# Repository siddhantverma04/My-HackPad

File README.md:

# My HackPad

A custom 3×3 macropad designed from scratch using KiCad, Fusion 360, and QMK.

The HackPad uses a Seeed Studio XIAO RP2040, 9 mechanical switches,
4 SK6812MINI-E RGB LEDs, a 128×32 OLED display, and custom QMK firmware.

## Features

- 3×3 mechanical key layout
- 4 SK6812MINI-E RGB LEDs
- 0.91" 128×32 SSD1306 OLED
- Seeed Studio XIAO RP2040
- Custom PCB
- Custom 3D-printed case
- QMK firmware

## HackPad Render

## Schematic

## PCB

## Case

The case was designed to fit the custom PCB, switches, OLED, and XIAO RP2040. 

## Firmware

The HackPad runs QMK firmware on the XIAO RP2040.

Current normal keymap:

| 1 | 2 | 3 |
|---|---|---|
| 4 | 5 | 6 |
| 7 | 8 | 9 |

Holding key 9 opens an RGB-control layer for changing effects,
hue, saturation, and brightness.

## Fully assembled!

The final and fully assembled hackpad!

## Bill of Materials

| Component | Amount |
|---|---:|
| Seeed Studio XIAO RP2040 | 1 |
| Cherry MX-compatible switches | 9 |
| 1N4148 diodes | 9 |
| SK6812MINI-E RGB LEDs | 4 |
| 0.91" 128×32 SSD1306 OLED | 1 |
| 1U keycaps | 9 |
| Custom PCB | 1 |
| 3D-printed top case / plate(I will print myself) | 1 |
| 3D-printed bottom case(I will print myself) | 1 |
| M3 screws | 4 |
| M3 heat-set inserts | 4 |

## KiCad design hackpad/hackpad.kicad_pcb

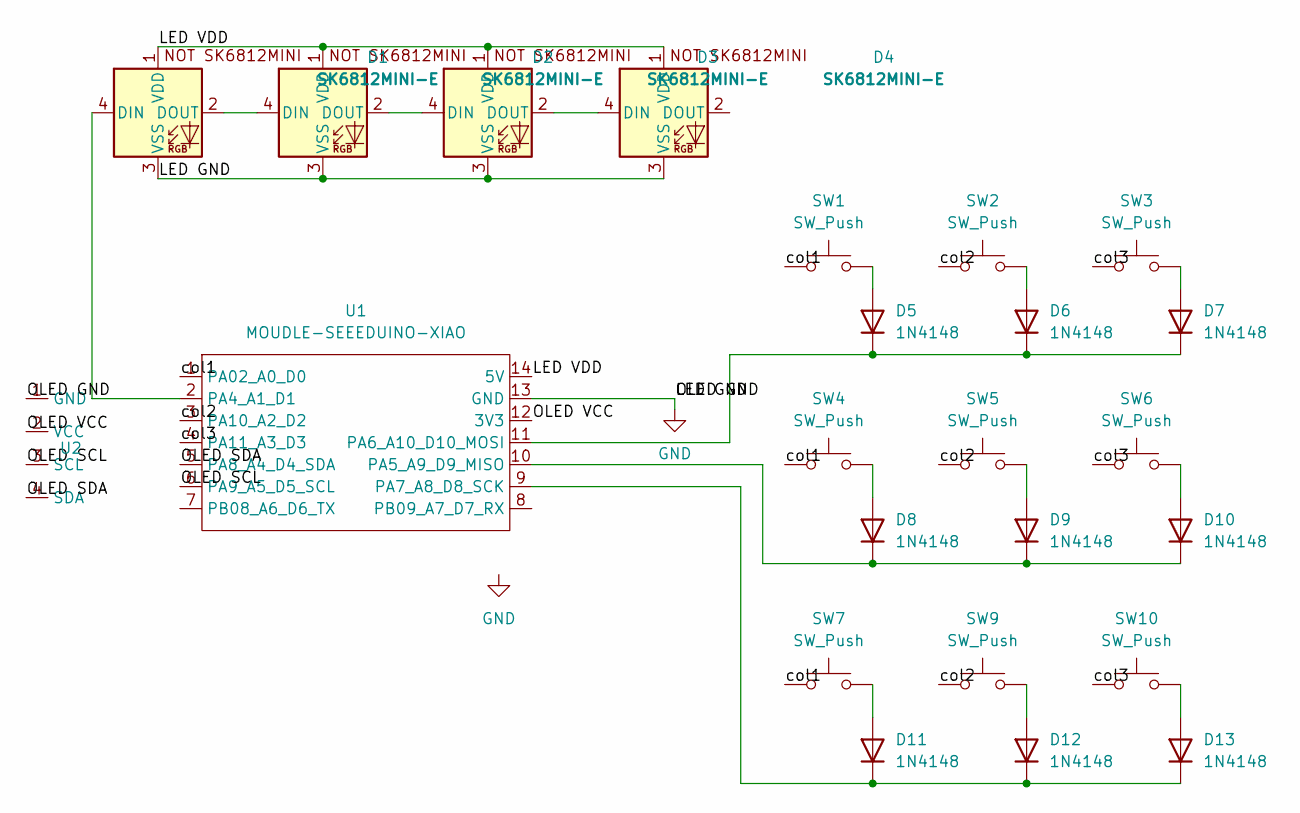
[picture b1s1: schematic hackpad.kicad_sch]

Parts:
D1, D2, D3, D4: SK6812MINI-E; LED_SK6812MINI-E_3.2x2.8mm_P1.5mm_ReverseMount
D5, D6, D7, D8, D9, D10, D11, D12, D13: 1N4148; D_DO-35_SOD27_P7.62mm_Horizontal
SW1, SW2, SW3, SW4, SW5, SW6, SW7, SW9, SW10: SW_Push; SW_Cherry_MX_1.00u_PCB
U1: MOUDLE-SEEEDUINO-XIAO; XIAO-Generic-Hybrid-14P-2.54-21X17.8MM
U2: SSD1306-0.91-OLED-4pin-128x32

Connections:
/<NO NET>: U1.5 (PA8_A4_D4_SDA), U2.4 (SDA)
/LED VDD: D1.1 (VDD), D2.1 (VDD), D3.1 (VDD), D4.1 (VDD), U1.14 (5V)
/OLED SCL: U1.6 (PA9_A5_D5_SCL), U2.3 (SCL)
/OLED VCC: U1.12 (3V3), U2.2 (VCC)
/col1: SW1.1, SW4.1, SW7.1, U1.1 (PA02_A0_D0)
/col2: SW2.1, SW5.1, SW9.1, U1.3 (PA10_A2_D2)
/col3: SW3.1, SW6.1, SW10.1, U1.4 (PA11_A3_D3)
GND: D1.3 (VSS), D2.3 (VSS), D3.3 (VSS), D4.3 (VSS), U1.13 (GND), U2.1 (GND)
unnamed: D1.4 (DIN), U1.2 (PA4_A1_D1)
unnamed: D1.2 (DOUT), D2.4 (DIN)
unnamed: D2.2 (DOUT), D3.4 (DIN)
unnamed: D3.2 (DOUT), D4.4 (DIN)
unnamed: D5.2 (A), SW1.2
unnamed: D5.1 (K), D6.1 (K), D7.1 (K), U1.11 (PA6_A10_D10_MOSI)
unnamed: D6.2 (A), SW2.2
unnamed: D7.2 (A), SW3.2
unnamed: D8.2 (A), SW4.2
unnamed: D9.2 (A), SW5.2
unnamed: D10.2 (A), SW6.2
unnamed: D8.1 (K), D9.1 (K), D10.1 (K), U1.10 (PA5_A9_D9_MISO)
unnamed: D11.2 (A), SW7.2
unnamed: D11.1 (K), D12.1 (K), D13.1 (K), U1.9 (PA7_A8_D8_SCK)
unnamed: D12.2 (A), SW9.2
unnamed: D13.2 (A), SW10.2

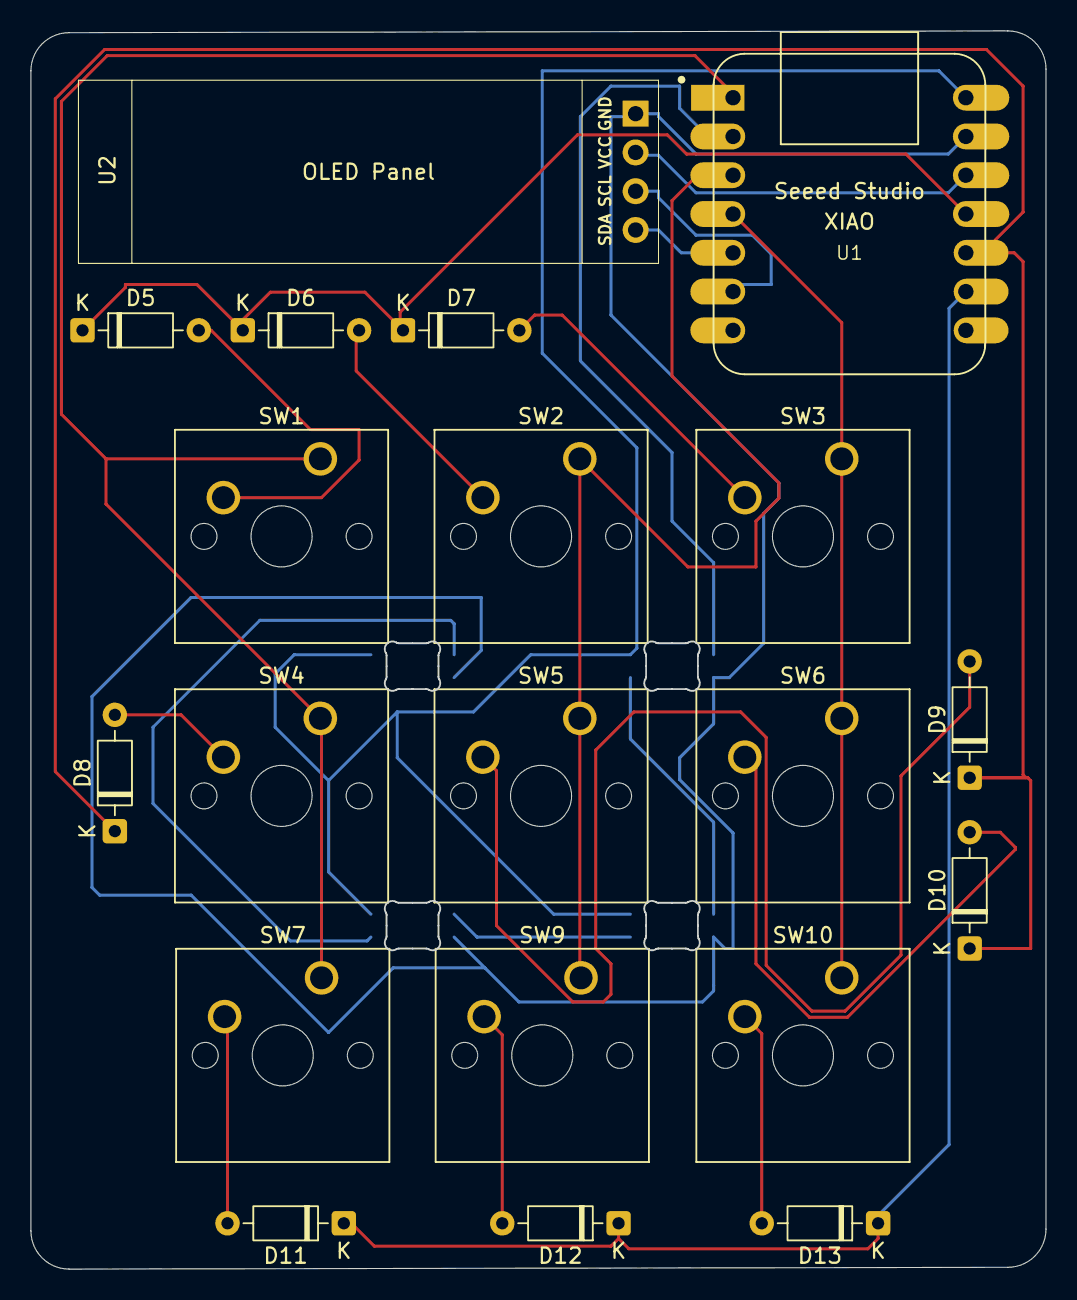
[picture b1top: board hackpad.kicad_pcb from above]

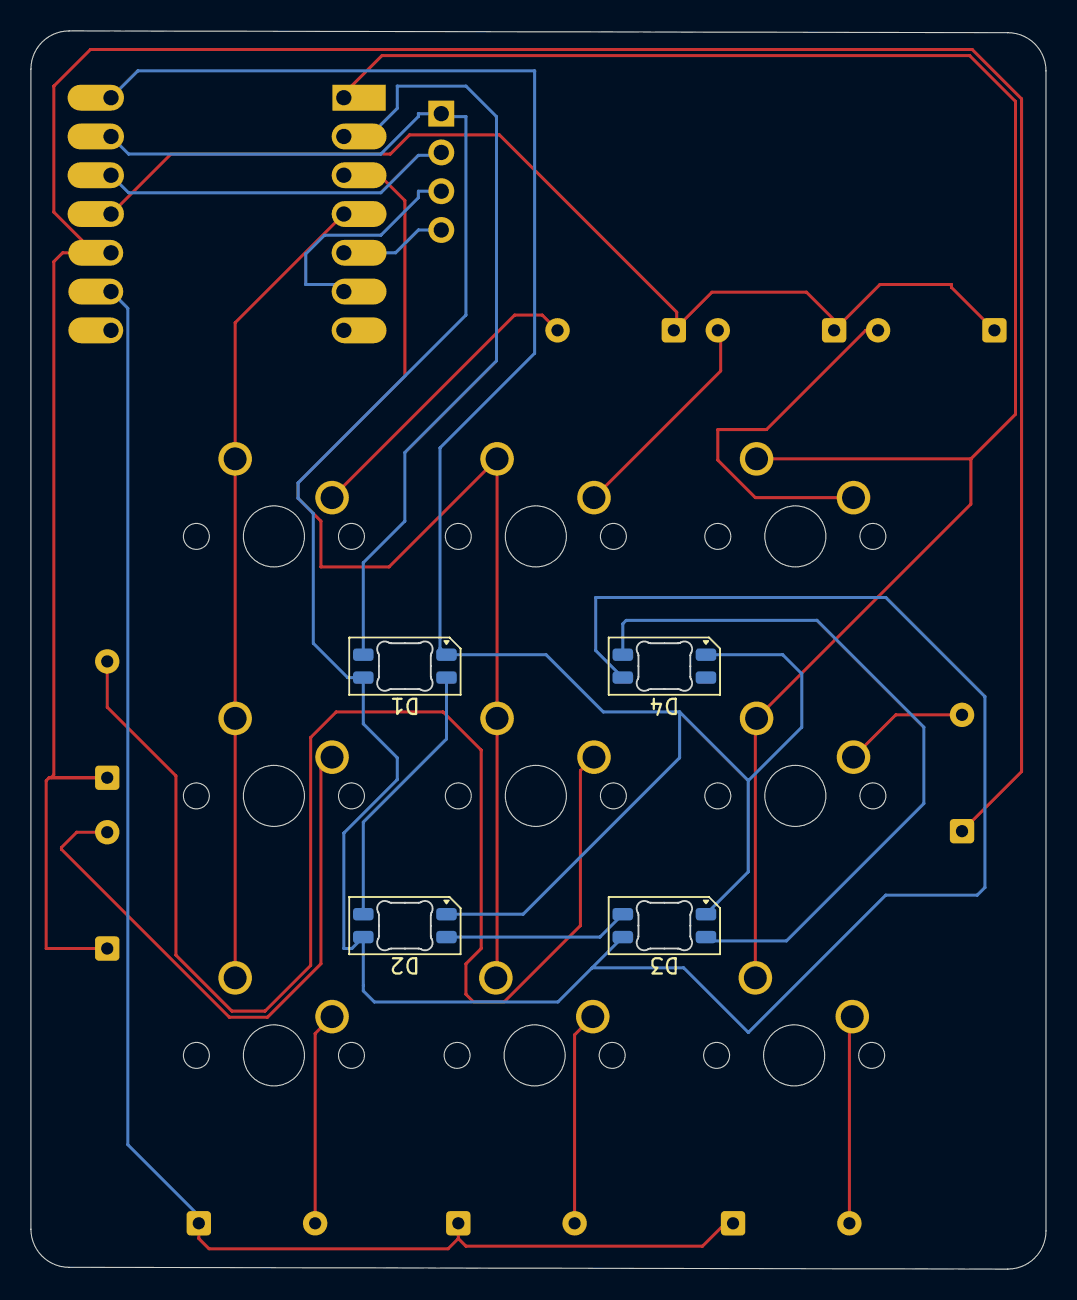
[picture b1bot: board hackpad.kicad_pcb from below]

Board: 2 copper layers, 66.5 x 81.1 mm, 24 parts (4 on the bottom side), 24 nets.
